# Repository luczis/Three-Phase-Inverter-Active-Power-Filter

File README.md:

# Three-Phase Inverter-Active Power Filter
An active power filter is responsible to provide power to loads while compensating for non-linearities and reactive power, that can degrade the main supply wave-form. It is also able to operate as an uninterruptible power supply

The topology consist of an active rectifier, supplying a battery bank. After that, the three-phase inverter is able to supply a load without reactive power or harmonics from the main.

The control loop is performed by a lead-lag controller.

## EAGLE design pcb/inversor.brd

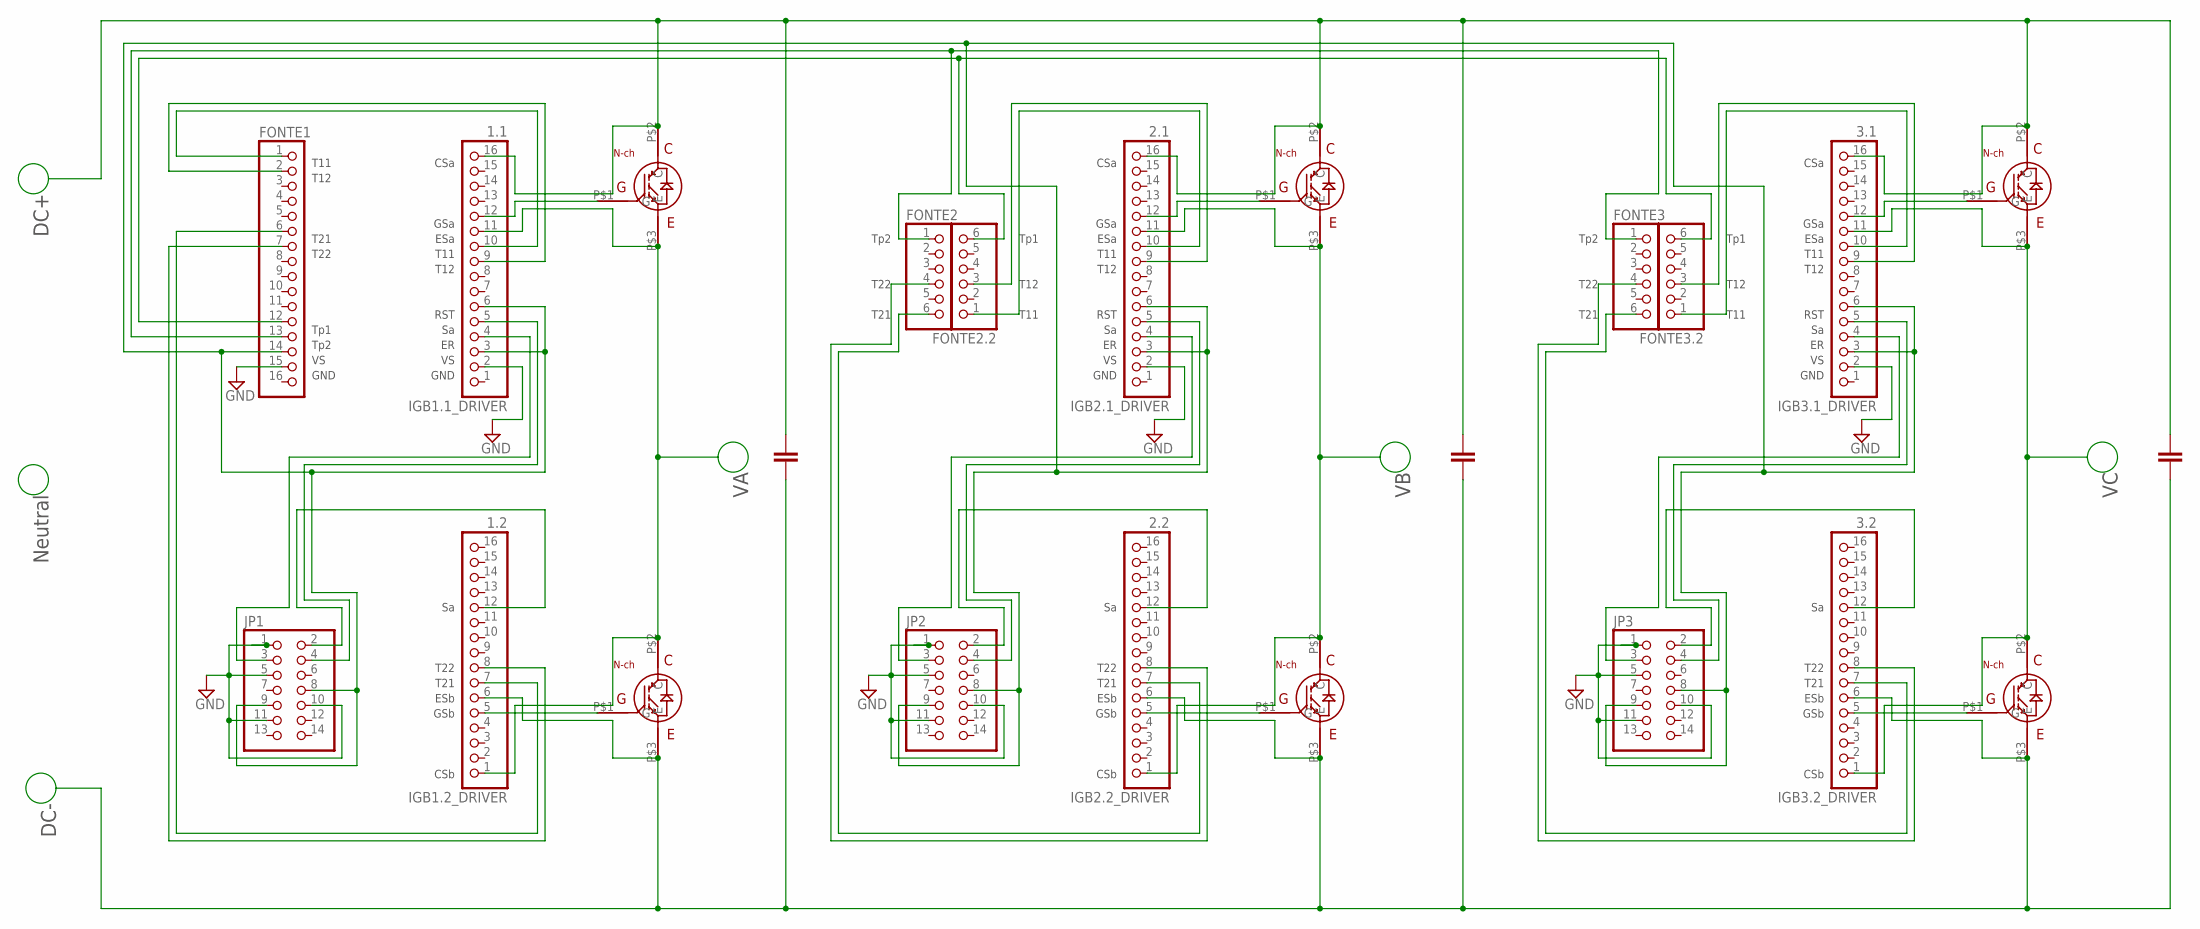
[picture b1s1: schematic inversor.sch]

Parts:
FONTE1: PINHD-1X16; 1X16
FONTE2, FONTE2.2, FONTE3, FONTE3.2: PINHD-1X6; 1X06
IGB1.1_DRIVER: 1.1; 1X16
IGB1.2_DRIVER: 1.2; 1X16
IGB2.1_DRIVER: 2.1; 1X16
IGB2.2_DRIVER: 2.2; 1X16
IGB3.1_DRIVER: 3.1; 1X16
IGB3.2_DRIVER: 3.2; 1X16
JP1, JP2, JP3: PINHD-2X7; 2X07
U$1, U$2, U$3, U$4, U$5, U$6: TO-247A; TO-247

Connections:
DC+: IGB1.1_DRIVER.16, IGB2.1_DRIVER.16, IGB3.1_DRIVER.16, U$1.P$2 (C), U$3.P$2 (C), U$5.P$2 (C)
DC-: IGB1.2_DRIVER.6, IGB2.2_DRIVER.6, IGB3.2_DRIVER.6, U$2.P$3 (E), U$4.P$3 (E), U$6.P$3 (E)
GND: FONTE1.15, IGB1.1_DRIVER.2, IGB2.1_DRIVER.2, IGB3.1_DRIVER.2, JP1.1, JP1.5, JP1.10, JP1.11, JP2.1, JP2.5, JP2.10, JP2.11, JP3.1, JP3.5, JP3.10, JP3.11
unnamed: IGB1.1_DRIVER.5, JP1.4
unnamed: IGB1.2_DRIVER.12, JP1.2
unnamed: IGB1.1_DRIVER.4, JP1.3
unnamed: FONTE1.1, IGB1.1_DRIVER.10
unnamed: FONTE1.2, IGB1.1_DRIVER.9
unnamed: FONTE1.7, IGB1.2_DRIVER.8
unnamed: FONTE1.6, IGB1.2_DRIVER.7
unnamed: IGB3.1_DRIVER.4, JP3.3
unnamed: IGB1.2_DRIVER.5, U$2.P$1 (G)
unnamed: IGB2.1_DRIVER.5, JP2.4
unnamed: IGB2.2_DRIVER.12, JP2.2
unnamed: IGB2.1_DRIVER.4, JP2.3
unnamed: FONTE2.2.1, IGB2.1_DRIVER.10
unnamed: FONTE2.2.3, IGB2.1_DRIVER.9
unnamed: FONTE2.4, IGB2.2_DRIVER.8
unnamed: FONTE2.6, IGB2.2_DRIVER.7
unnamed: IGB2.1_DRIVER.12, U$3.P$1 (G)
unnamed: IGB2.2_DRIVER.5, U$4.P$1 (G)
unnamed: IGB3.1_DRIVER.5, JP3.4
unnamed: IGB3.2_DRIVER.12, JP3.2
unnamed: FONTE3.2.1, IGB3.1_DRIVER.10
unnamed: FONTE3.2.3, IGB3.1_DRIVER.9
unnamed: FONTE3.4, IGB3.2_DRIVER.8
unnamed: FONTE3.6, IGB3.2_DRIVER.7
unnamed: IGB3.1_DRIVER.12, U$5.P$1 (G)
unnamed: IGB3.2_DRIVER.5, U$6.P$1 (G)
TP1: FONTE1.12, FONTE2.2.6, FONTE3.2.6
TP2: FONTE1.13, FONTE2.1, FONTE3.1
VA: IGB1.1_DRIVER.11, IGB1.2_DRIVER.1, U$1.P$3 (E), U$2.P$2 (C)
VB: IGB2.1_DRIVER.11, IGB2.2_DRIVER.1, U$3.P$3 (E), U$4.P$2 (C)
VC: IGB3.1_DRIVER.11, IGB3.2_DRIVER.1, U$5.P$3 (E), U$6.P$2 (C)
VS: FONTE1.14, IGB1.1_DRIVER.3, IGB1.1_DRIVER.6, IGB2.1_DRIVER.3, IGB2.1_DRIVER.6, IGB3.1_DRIVER.3, IGB3.1_DRIVER.6, JP1.8, JP1.9, JP2.8, JP2.9, JP3.8, JP3.9
VS1: IGB1.1_DRIVER.12, U$1.P$1 (G)

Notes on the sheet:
CSa GSa ESa T11 T12 RST Sa ER VS GND
Sa T22 T21 ESb GSb CSb
T11 T12 T21 T22 Tp1 Tp2 VS GND
DC-
Neutral
DC+
Tp2 T22 T21
Tp1 T12 T11

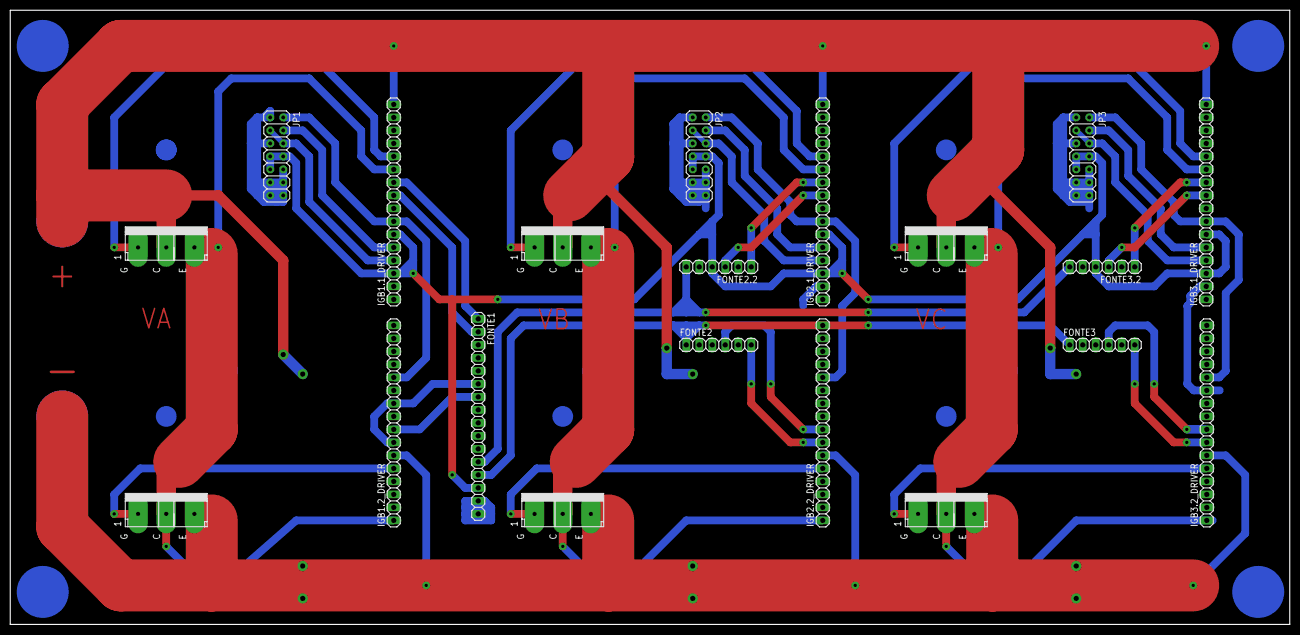
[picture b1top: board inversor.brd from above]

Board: 2 copper layers, 250.0 x 120.0 mm, 20 parts (0 on the bottom side), 36 nets.

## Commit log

2024-01-21 Added files
